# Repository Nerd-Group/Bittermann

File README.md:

# Bittermann
Happy Birthday, Martin

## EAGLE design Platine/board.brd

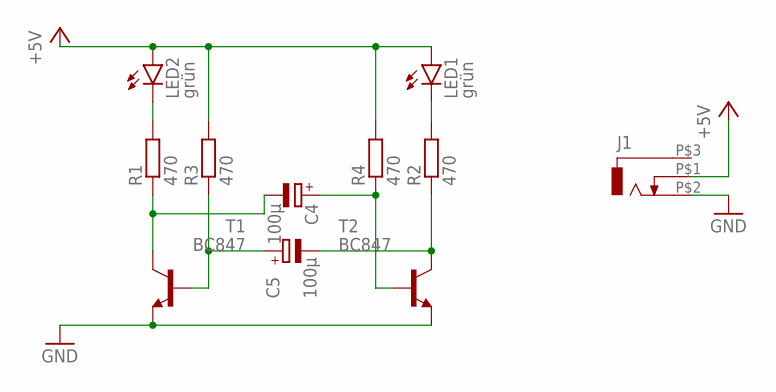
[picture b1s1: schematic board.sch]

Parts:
C4, C5: 100µ; 153CLV-0605
J1: RASM7X2
LED1, LED2: grün; CHIPLED_0805
R1, R2, R3, R4: 470; R0805
T1, T2: BC847; SOT23

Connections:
+5V: J1.P$1 (2), LED1.A, LED2.A, R3.2, R4.2
GND: J1.P$2 (3), T1.2 (E), T2.2 (E)
unnamed: LED2.C, R1.2
unnamed: LED1.C, R2.2
unnamed: C4.-, R1.1, T1.3 (C)
unnamed: C5.-, R2.1, T2.3 (C)
unnamed: C4.+, R4.1, T2.1 (B)
unnamed: C5.+, R3.1, T1.1 (B)

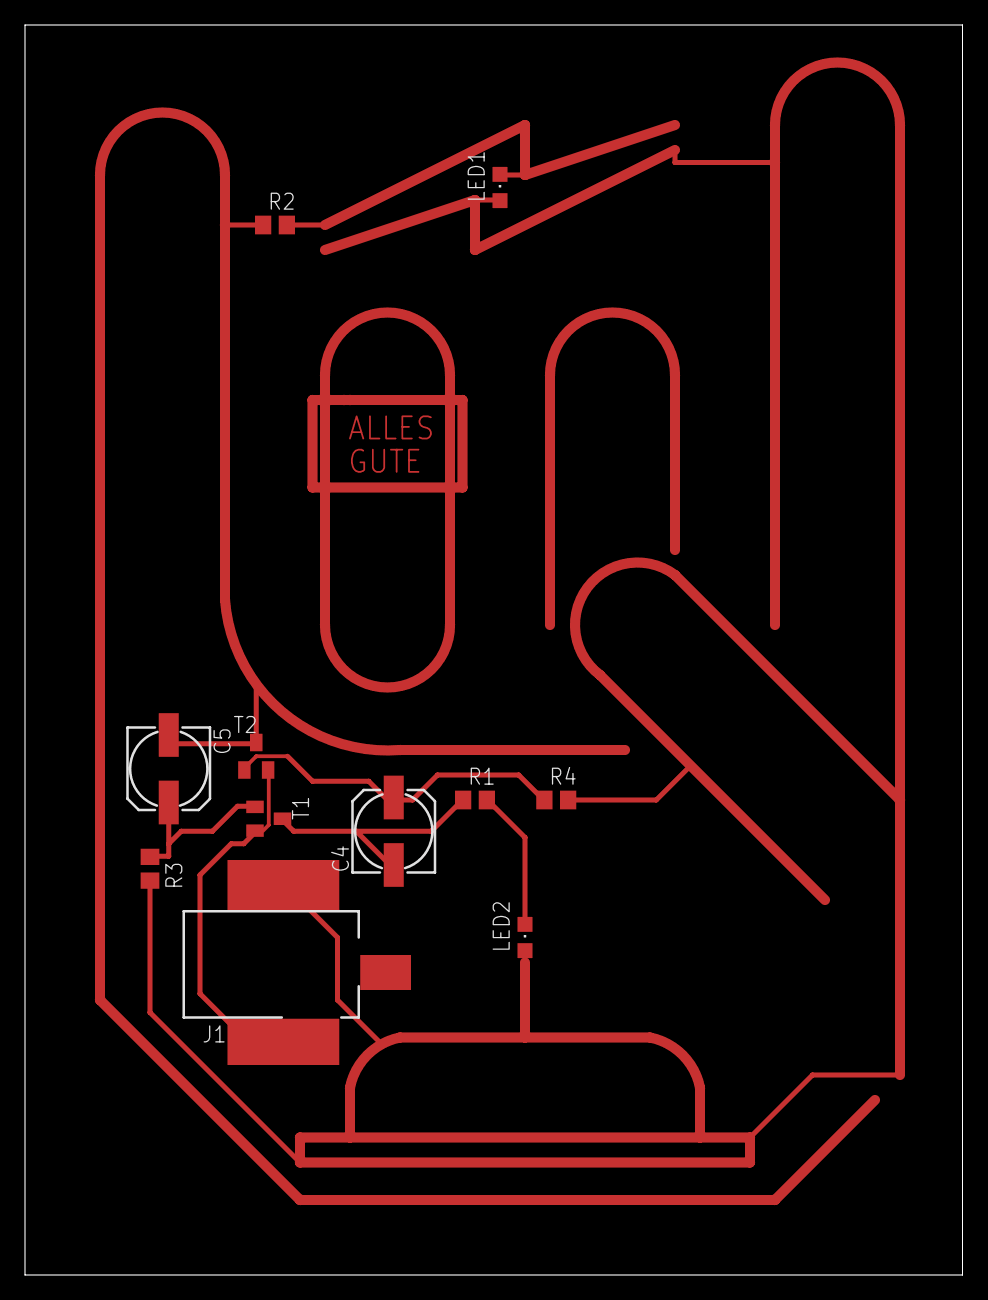
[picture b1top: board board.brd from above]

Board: 2 copper layers, 75.0 x 100.0 mm, 11 parts (0 on the bottom side), 8 nets.

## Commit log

2021-03-03 Platine fertig
2021-03-07 Update PCB
2021-03-08 Update Platine: SMD Hohlstecker + Wire vergessen
2021-03-12 no text, leave the commit message out
